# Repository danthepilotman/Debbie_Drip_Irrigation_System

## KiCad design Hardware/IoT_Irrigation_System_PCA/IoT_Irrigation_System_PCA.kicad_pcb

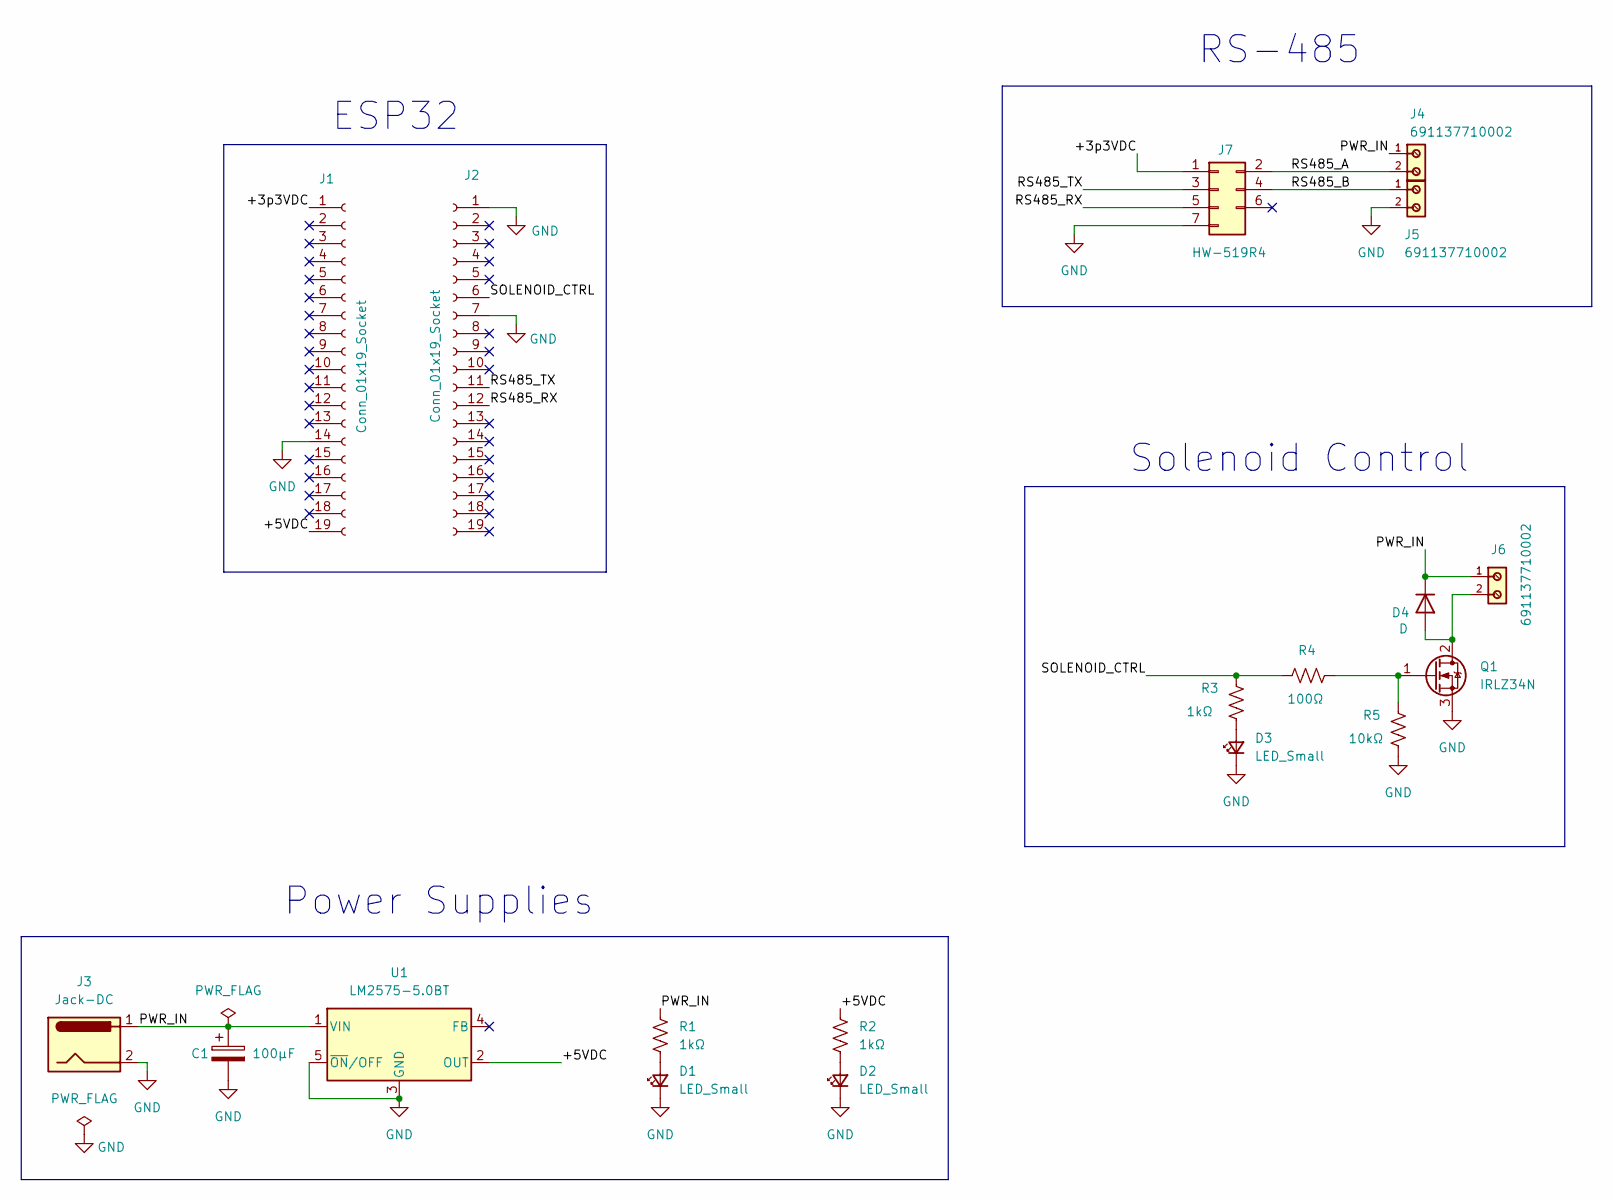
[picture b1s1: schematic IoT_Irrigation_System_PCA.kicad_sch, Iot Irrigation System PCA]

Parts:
C1: 100µF; CP_Radial_D8.0mm_P3.80mm
D1, D2, D3: LED_Small; LED_D3.0mm
D4: D; D_DO-15_P12.70mm_Horizontal
J1, J2: Conn_01x19_Socket; PinSocket_1x19_P2.54mm_Vertical
J3: Jack-DC; BarrelJack_Horizontal
J4, J5, J6: 691137710002; DigiKey_Part_Number 732-10955-ND
J7: HW-519R4
Q1: IRLZ34N; TO-220-3_Vertical
R1, R2, R3: 1kΩ; R_Axial_DIN0207_L6.3mm_D2.5mm_P10.16mm_Horizontal
R4: 100Ω; R_Axial_DIN0207_L6.3mm_D2.5mm_P10.16mm_Horizontal
R5: 10kΩ; R_Axial_DIN0207_L6.3mm_D2.5mm_P10.16mm_Horizontal
U1: LM2575-5.0BT; TO-220-5_Vertical

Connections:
/+3p3VDC: J1.1, J7.1
/+5VDC: J1.19, R2.1, U1.2 (OUT)
/PWR_IN: C1.1, D4.1 (K), J3.1, J4.1, J6.1, R1.1, U1.1 (VIN)
/RS485_A: J4.2, J7.2
/RS485_B: J5.1, J7.4
/RS485_RX: J2.12, J7.5
/RS485_TX: J2.11, J7.3
/SOLENOID_CTRL: J2.6, R3.1, R4.2
GND: C1.2, D1.1 (K), D2.1 (K), D3.1 (K), J1.14, J2.1, J2.7, J3.2, J5.2, J7.6, J7.7, Q1.3 (S), R5.2, U1.3 (GND), U1.5 (~ON/OFF)
unnamed: D1.2 (A), R1.2
unnamed: D2.2 (A), R2.2
unnamed: D3.2 (A), R3.2
unnamed: D4.2 (A), J6.2, Q1.2 (D)
unnamed: Q1.1 (G), R4.1, R5.1

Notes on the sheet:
RS-485
ESP32
Solenoid Control
Power Supplies

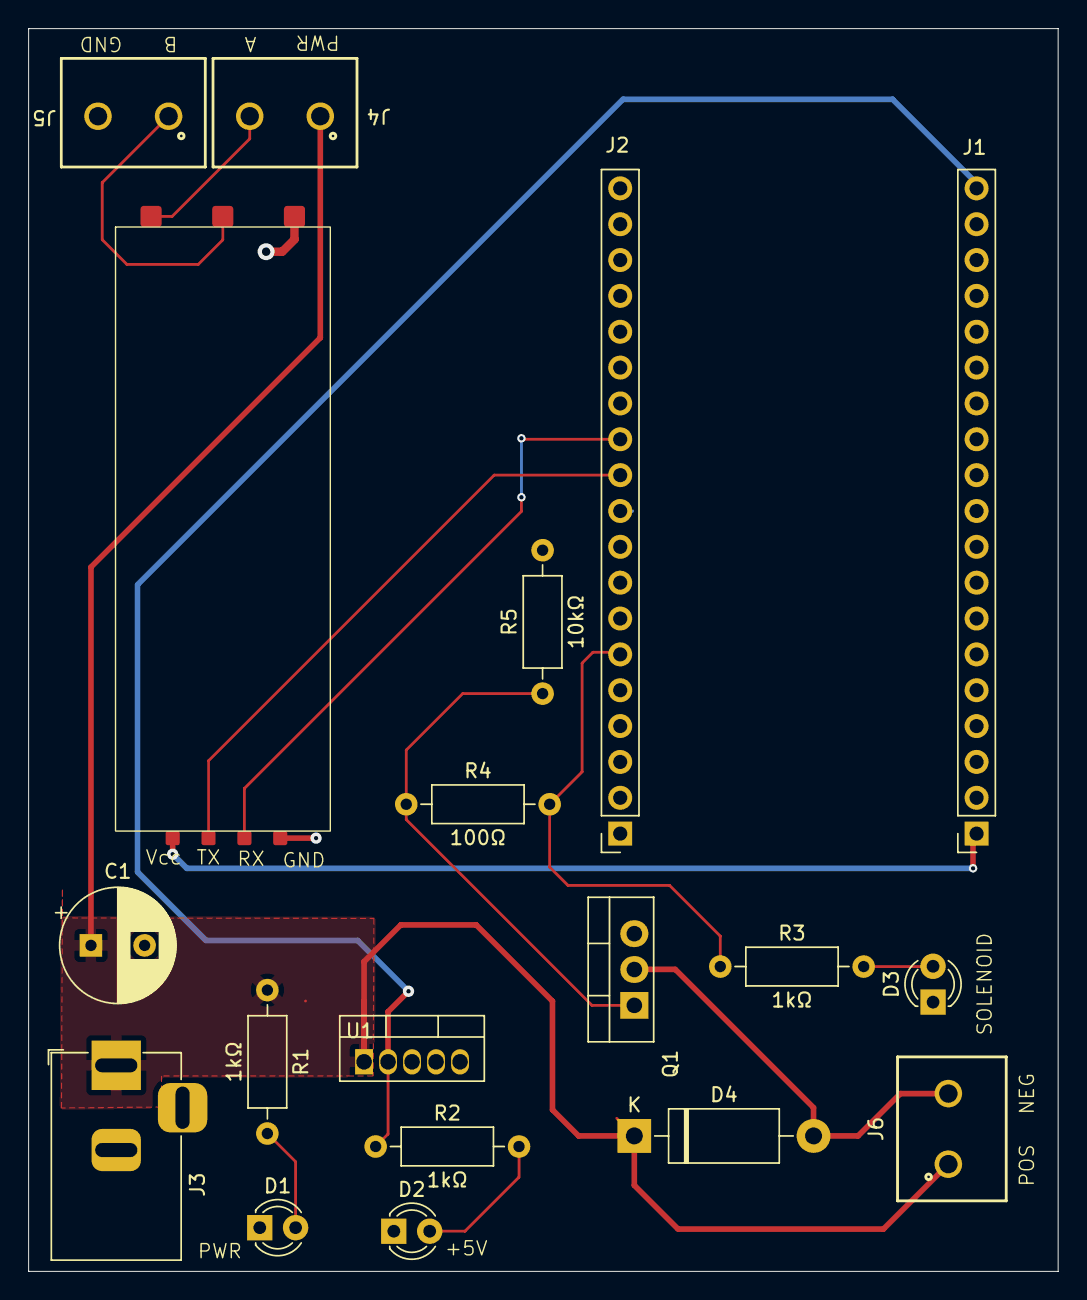
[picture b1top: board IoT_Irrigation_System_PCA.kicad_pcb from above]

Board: 2 copper layers, 73.0 x 88.1 mm, 19 parts (0 on the bottom side), 14 nets.

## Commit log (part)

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2026-01-06 1. Fixed issue with not reading TalkBack commands. 2. Modified to use multiple functions and files. 3. Modified to use RTP to keep track of watering times.
2026-01-06 1. Added communication error checking. 2. Cleaned up and upgraded print statements.
2026-01-07 1. Added folder for Matlab scripts and Reference documents 2. Removed Modbus library from platformio.ini 3. Modified to use out own custom RS485 code 4. Added ThingSpeak channel status timestamp to a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
2026-01-08 1. Modified duration, watering_needed, solenoid_closed to global variables. 2. Removed build option definitions 3. Added sleep timer function to handle dynamic sleep cycles 4. Added reporting of sole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
2026-01-08 1. Added Watering Timeline visualization script
2026-01-09 Modified get_settings to better utilize the JSON structure of the reply message from TS
2026-01-10 1. Removed multiple NTP serves to help avoid RTC skips 2. Updated MATLAB script to better use TalkBack to communicate operating parameters
2026-01-11 Added TS timestamp checking
2026-01-13 1. Fixed issue with missing "\n" in some debug print statements 2. Removed delay from loop() 3. Changed NTP update timeout to stop after 5 tries
2026-01-14 1. Changed timestamp format to "Wed Jan 14,2025 06:00 AM" 2. Increased TB delay to 180s
2026-01-15 1. Added KiCAD PCB design files 2. Added MOSFET and RS485 module reference files 3. Changed TB delay to 30s 4. Added "\r" for better serial printing
2026-01-16 1. Added Wifi connectivity logic 2. Fixed error in getSettings() tries loop 3. Modified TB delay to 180s (3 min) 4. Updates to PCB design
2026-01-16 Update to gitignore
2026-01-16 Updated PCB
    Spaced ESP32 socket headers to 25.4mm
    Moved RS485 and power supply components
2026-01-16 Added ESP322 Dev Kit V4 pinout to reference docs
2026-01-16 Updated drawio Program Flow Diagrams
2026-01-18 Added TB updating of wake schedule and RSSI logging to TS channel # 2
2026-01-18 Added wake up schedule updating to Matlab "Send data to ESP32" script
2026-01-20 1.Added LittleFS to store TB settings 2. Moved functions from thingspeak to helper file 3. Modified setting structure to store TB values 4. Added precompiler directives to allow for no soil sensor an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
2026-01-29 Modified how multiple HTTP request attempts are handled
2026-01-31 Added comments and changed for Json documents are used
2026-01-31 Updated "tries" logic for repeated HTTP attempts
2026-01-31 Corrected weather JSON pop
2026-03-30 1. Added ping_ThingSpeak() function to transmit status message after power on or reset button pressed 2. Moved Wifi RSSI reporting to its own function
2026-03-30 1. Added #ifdef to debug print statements 2. Changed WX forecast to use NWS 3. Removed local processing of WX forecast 4. Updated MatLab scripts to match NWS WX forecast
2026-04-02 Updated rainExpectedSoon() function to use NWS JSON
2026-04-03 1. Restructured code to only read watering parameters from ThingSpeak TalkBack. 2. Removed rain_expected and watering_needed from TS. 3. Added minimum rain probability. 4. Will now only compute rain 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
2026-04-07 Updated custom partitions to allow for core dump
2026-04-19 1. Updated board type in platform.ini 2. Added OLED capability 3. Split off ThingSpeak updating from getting new reading 4. Added button functionality to allow for scrolling of OLED pages 5. Moved re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
2026-04-20 1. Converted ThingSpeak communication to function though use of a class 2. Adjusted TS PROCESS DELAY to 20s to allow for more headroom between updates 3. Added a few more OLED print messages
2026-04-24 1. Changed board to ESP32 S3 devkitc-1 2. Added OTA firmware update capability 3. Added RBG led and OLED notifications 4. Modified sendThingSpeak() to only check for response code instead of checking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
2026-04-24 1. Updated Release repo location 2. Updated loop() to better handle wake up cause
2026-05-02 1. Moved DBG print statements inside of #ifdef 2. Changed over to DEBBIES HOUSE parameters
2026-05-02 1. Added WX pahe to OLED pages 2. Added display_message() function to clean up OLED display calls
2026-05-04 1. Added release build Python scipt 2. Fixed RS485 TX/RX pin assignments 3. Fixed double url encoding error of status message 4. Removed firmware folder as Python script updates Release repo directly
2026-05-04 1. Added keyboard shortcut capability for release update Python script
2026-05-05 1. Removed good_cycle variable 2. Adjusted OLED rotation to 0 degrees 3. Rearranged handle_sample_state() to allow forcomputing of watering needed befor sending ThingSpeak Update
2026-05-06 1. Modified status string to print out SW version
2026-05-09 1. Added created_at timestamp field to ThingSpeak updates 2. Modified Timestamp function to allow for diffrent formats
2026-05-09 1. Added POST Javascipt for testing purposes 2. Updated firmware version to 1.0.13 3. Slightly modified HTTP body string construction order
2026-05-20 v1.0.14
2026-05-26 v1.0.15
2026-05-26 v1.0.15 take 2
2026-06-06 1. Updated SW version to 1.0.16 2. Added LAMP DB server upload capability 3. Added static IP setting for Palm Bay location 4. Some stylistic updates
